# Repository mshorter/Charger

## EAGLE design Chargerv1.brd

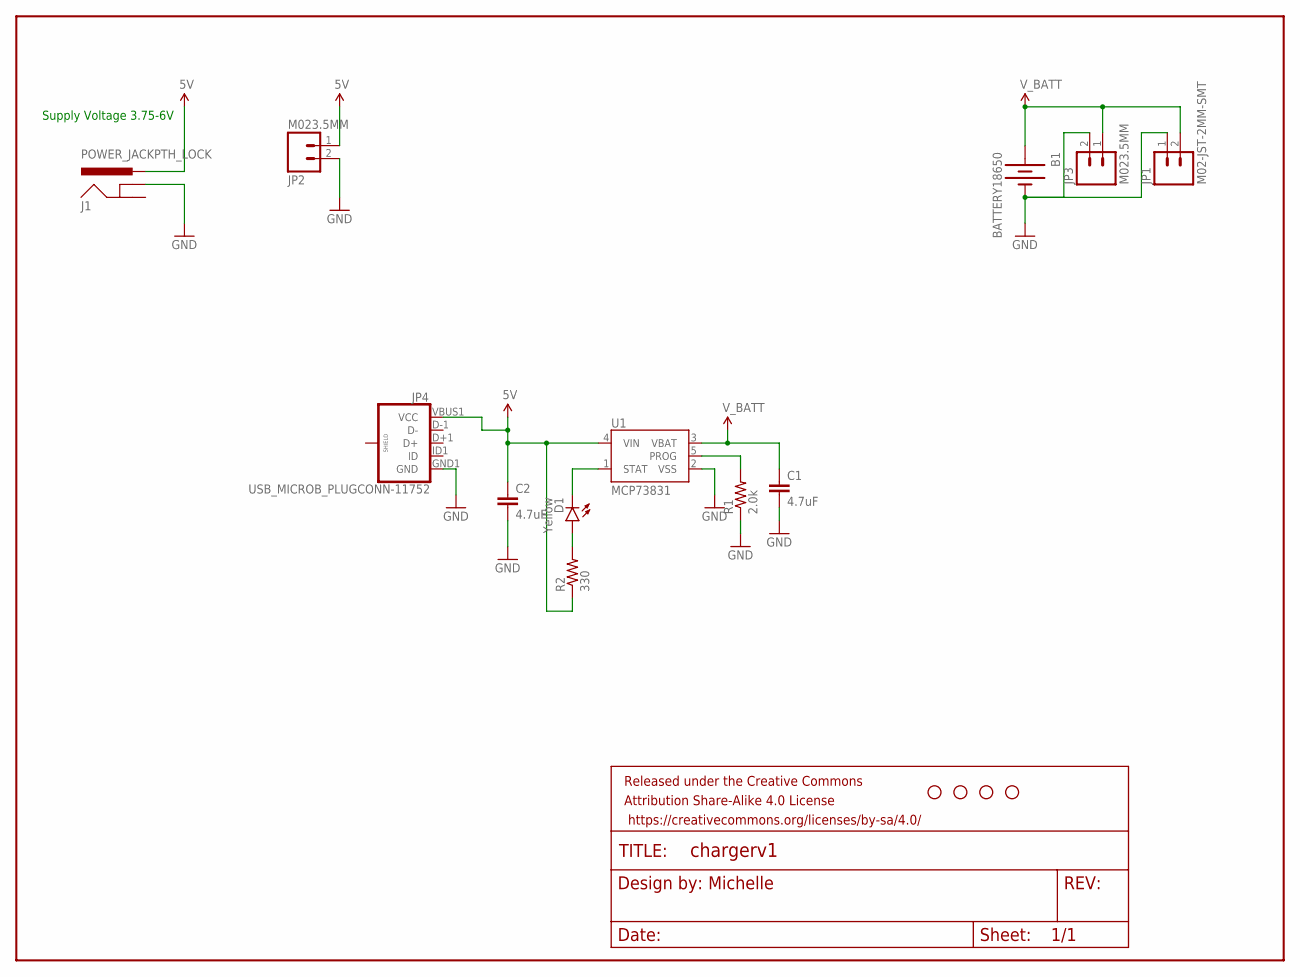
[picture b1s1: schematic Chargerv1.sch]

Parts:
B1: BATTERY18650; 18650-HOLDER
C1, C2: 4.7uF; 0603-CAP
D1: Yellow; LED-0603
FRAME1: FRAME-LETTER; CREATIVE_COMMONS
J1: POWER_JACKPTH_LOCK; POWER_JACK_PTH_LOCK
JP1: M02-JST-2MM-SMT; JST-2-SMD
JP2, JP3: M023.5MM; SCREWTERMINAL-3.5MM-2
JP4: USB_MICROB_PLUGCONN-11752; USB-B-MICRO-SMD_V03
R1: 2.0k; 0603-RES
R2: 330; 0603-RES
STANDOFF1, STANDOFF2, STANDOFF3, STANDOFF4: STAND-OFF
U1: MCP73831; SOT23-5

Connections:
5V: C2.1, J1.PWR, JP2.1, JP4.VBUS1 (VCC), R2.1, U1.4 (VIN)
GND: B1.GND@1 (-), C1.2, C2.2, J1.GNDBREAK, JP1.1 (2), JP2.2, JP3.2, JP4.GND1 (GND), R1.1, U1.2 (VSS)
unnamed: D1.A, R2.2
unnamed: D1.C, U1.1 (STAT)
unnamed: R1.2, U1.5 (PROG)
V_BATT: B1.PWR@1 (+), C1.1, JP1.2 (1), JP3.1, U1.3 (VBAT)

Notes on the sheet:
Supply Voltage 3.75-6V

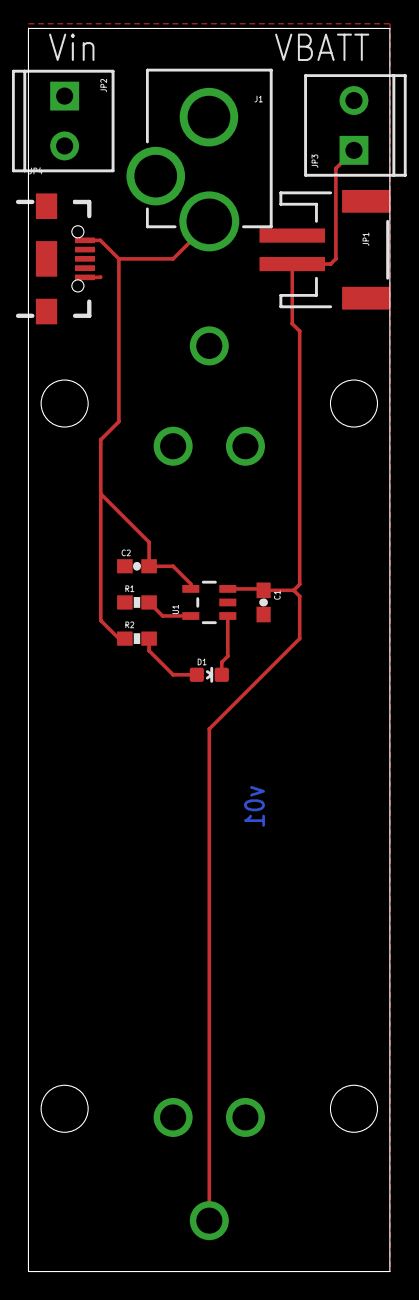
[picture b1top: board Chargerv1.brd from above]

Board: 2 copper layers, 25.4 x 87.3 mm, 17 parts (1 on the bottom side), 6 nets.

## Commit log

2015-01-12 Initial schematic/board design
2015-01-12 Routed Board
2015-02-12 Ready for Itead order
    Final version with gerbers as sent to Itead (ordered 1/30, received
    2/11)

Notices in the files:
parts and their libraries:
SparkFun-PowerIC: Licensing: CC v3.0 Share-Alike You are welcome to use this library for commercial purposes.
SparkFun-Aesthetics: Released under the Creative Commons Attribution Share-Alike 4.0 License
SparkFun-Aesthetics: https://creativecommons.org/licenses/by-sa/4.0
